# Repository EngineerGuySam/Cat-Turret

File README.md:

# Cat-Turret
A Raspberry Pi 4–powered pan-and-tilt water gun that uses a camera and YOLO machine learning to detect cats on counters. Built with Python, the system tracks movement, aims with servos, and sprays water to deter unwanted feline adventures.

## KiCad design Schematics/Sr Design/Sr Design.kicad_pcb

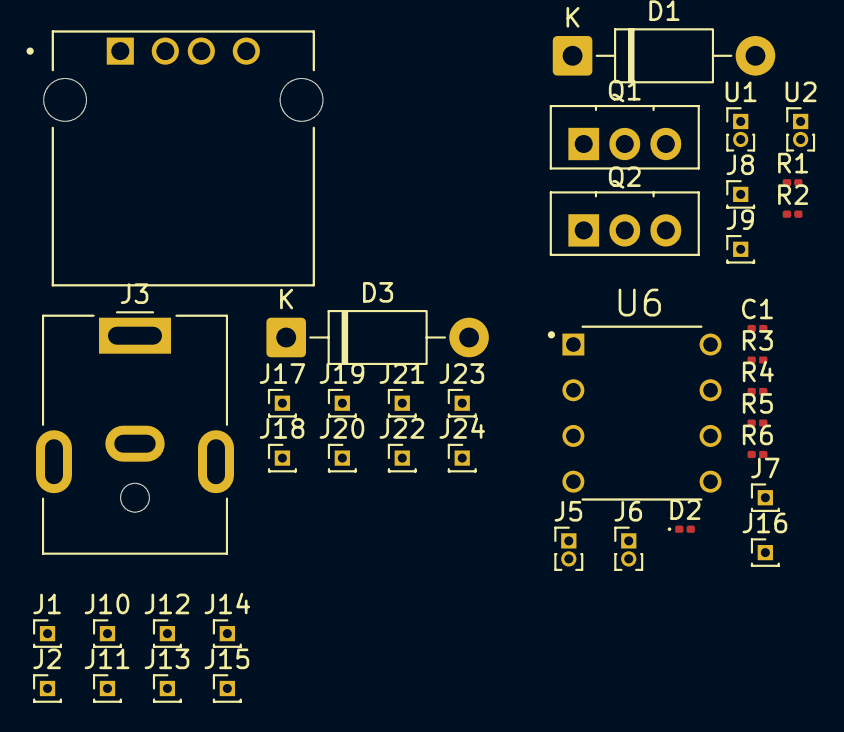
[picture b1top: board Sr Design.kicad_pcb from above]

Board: 2 copper layers, 39 parts (0 on the bottom side), 18 nets, no tracks yet.

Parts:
C1: 1u F; C_0201_0603Metric
D1, D3: 1N5818; D_DO-41_SOD81_P10.16mm_Horizontal
D2: LED; LED_0201_0603Metric
J1: GPIO 21; PinHeader_1x01_P1.00mm_Vertical
J2: Pan 5V; PinHeader_1x01_P1.00mm_Vertical
J3: Barrel_Jack; BarrelJack_CUI_PJ-063AH_Horizontal
J4: USB-A1HSW6; OST_USB-A1HSW6
J5: Tanner's Capacitor; PinHeader_1x02_P1.00mm_Vertical
J6: Water Float Switch; PinHeader_1x02_P1.00mm_Vertical
J7: GPIO 22; PinHeader_1x01_P1.00mm_Vertical
J8: GPIO 23; PinHeader_1x01_P1.00mm_Vertical
J9: GPIO 24; PinHeader_1x01_P1.00mm_Vertical
J10, J16: GPIO 20; PinHeader_1x01_P1.00mm_Vertical
J11: Pan GPIO; PinHeader_1x01_P1.00mm_Vertical
J12: Pan GND; PinHeader_1x01_P1.00mm_Vertical
J13: Tilt 5V; PinHeader_1x01_P1.00mm_Vertical
J14: Tilt GPIO; PinHeader_1x01_P1.00mm_Vertical
J15: Tilt GND; PinHeader_1x01_P1.00mm_Vertical
J17: Pi4 12V; PinHeader_1x01_P1.00mm_Vertical
J18: Pi4 GND; PinHeader_1x01_P1.00mm_Vertical
J19: Pi Buck 5V; PinHeader_1x01_P1.00mm_Vertical
J20: Pi Buck GND; PinHeader_1x01_P1.00mm_Vertical
J21: Servo 12V; PinHeader_1x01_P1.00mm_Vertical
J22: Servo GND; PinHeader_1x01_P1.00mm_Vertical
J23: Servo Buck 7V; PinHeader_1x01_P1.00mm_Vertical
J24: Servo Buck GND; PinHeader_1x01_P1.00mm_Vertical
Q1, Q2: C6144; TO-126-3_Vertical
R1, R2: 300; R_0201_0603Metric
R3, R4, R5: 10k; R_0201_0603Metric
R6: 330; R_0201_0603Metric
U1, U2: PinHeader_1x02_P1.00mm_Vertical
U6: LM555CN; DIP762W46P254L960H508Q8

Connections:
+5V Pi: D3.1 (K), J4.1 (VBUS)
+7V: J2.1, J13.1, J23.1
+12V: D1.1 (K), J3.1, J17.1, J21.1, R3.1, U6.8 (VCC)
GND: C1.2, D2.1 (K), J3.2, J4.4 (GND), J5.2, J12.1, J15.1, J18.1, J20.1, J22.1, J24.1, Q1.1 (E), Q2.1 (E), R5.2, U6.1 (GND)
unnamed: D1.2 (A), Q1.2 (C)
unnamed: D2.2 (A), R6.2
unnamed: D3.2 (A), J19.1
unnamed: J1.1, J14.1
unnamed: J5.1, J6.2, R4.2, U6.2 (TRIGGER), U6.6 (THR)
unnamed: C1.1, J6.1
unnamed: J7.1, R6.1
unnamed: J8.1, R1.1
unnamed: J9.1, R2.1
unnamed: J10.1, J11.1
unnamed: J16.1, R5.1, U6.3 (OUT)
unnamed: Q1.3 (B), R2.2
unnamed: Q2.3 (B), R1.2
unnamed: R3.2, R4.1, U6.4 (RESET), U6.7 (DISCH)

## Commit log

2025-08-29 Test push on windows
2025-08-29 big booba
2025-08-29 Commiting from Pi Test -Sam H
2025-08-29 censored sophia.txt
2025-08-29 idek
2025-09-03 Adding schematics, Schematics are done in KiCAD
2025-09-03 SCHM updated need to figure out how we want to apply our power design.
2025-09-05 Tanners gpio code for the pump and solenoid
2025-09-05 This is tanners code for the solenoid and pump
2025-09-08 Schematics To include servos
2025-09-08 Servos included in schematics now
2025-09-12 schematics updated
2025-09-19 New Sophia Branch.
    Mostly just cleaned up the scripts to look better, I tried not to change anything. The only thing I changed was Sam's pan_tilt.py script where I removed the confidence threshold stuff, which can be u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
    Otherwise the main.py is the script that will control OOOoOoO all the other scripts. The pan_preview.py is the script to test the live preview/yolo camera with sams pan and tilt.
2025-09-19 schematics update
2025-09-19 v3 code is pan_tilt
2025-10-04 scematics update
2025-10-04 pcb parts
